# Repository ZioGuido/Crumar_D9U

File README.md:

# GMLAB_D9U
This is the Arduino project for GMLAB D9U, an open source DIY drawbar controller.
Please refer to the included PDF for details about the project, the code and the electronics.

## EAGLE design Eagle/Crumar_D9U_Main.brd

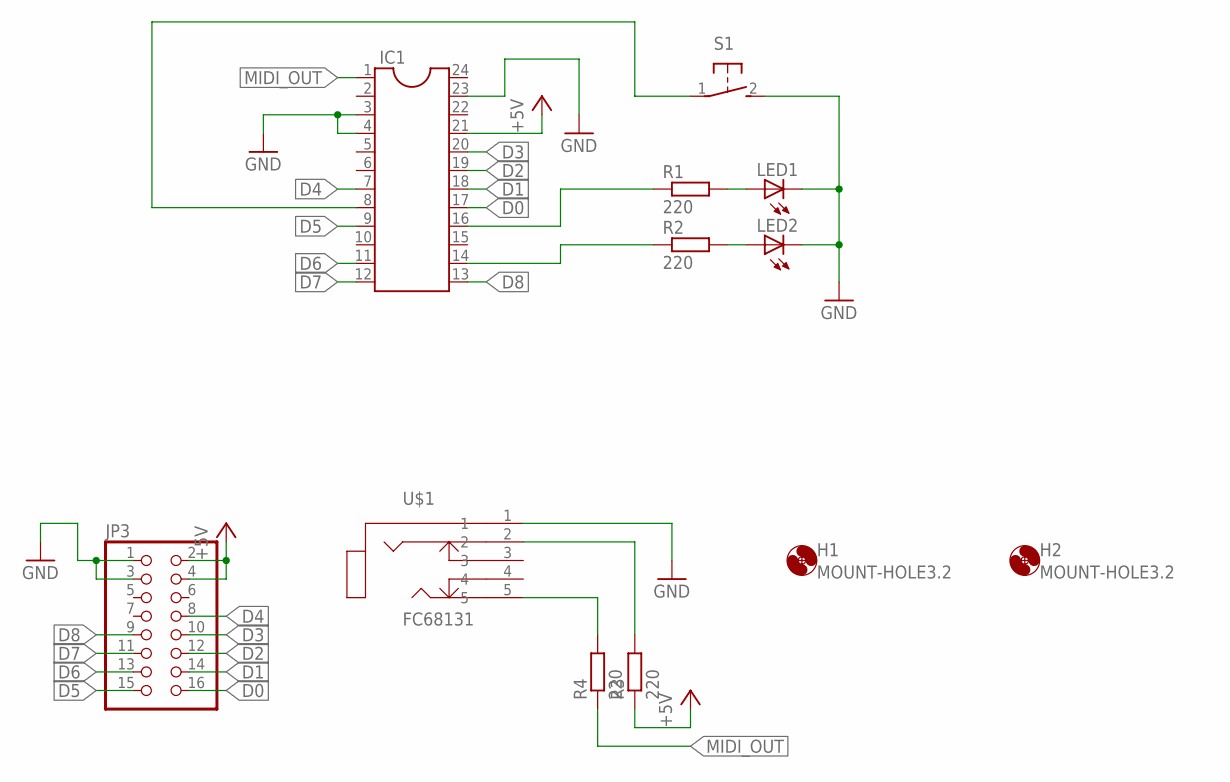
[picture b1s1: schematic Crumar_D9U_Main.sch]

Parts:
H1, H2: MOUNT-HOLE3.2; 3,2
IC1: DIL24-6
JP3: PINHD-2X8; 2X08
LED1, LED2: LED3MM
R1, R2, R3, R4: 220; 0207/7
S1: 31-XX; B3F-31XX
U$1: FC68131; FC68131-5P

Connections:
+5V: IC1.21, JP3.2, JP3.4, R3.1
D0: IC1.17, JP3.16
D1: IC1.18, JP3.14
D2: IC1.19, JP3.12
D3: IC1.20, JP3.10
D4: IC1.7, JP3.8
D5: IC1.9, JP3.15
D6: IC1.11, JP3.13
D7: IC1.12, JP3.11
D8: IC1.13, JP3.9
GND: IC1.3, IC1.4, IC1.23, JP3.1, JP3.3, LED1.K (C), LED2.K (C), S1.2 (S), U$1.1
LED1: IC1.16, R1.1
LED2: IC1.14, R2.1
MIDI_OUT: IC1.1, R4.1
unnamed: LED2.A, R2.2
unnamed: LED1.A, R1.2
unnamed: R3.2, U$1.2
unnamed: R4.2, U$1.5
SW: IC1.8, S1.1

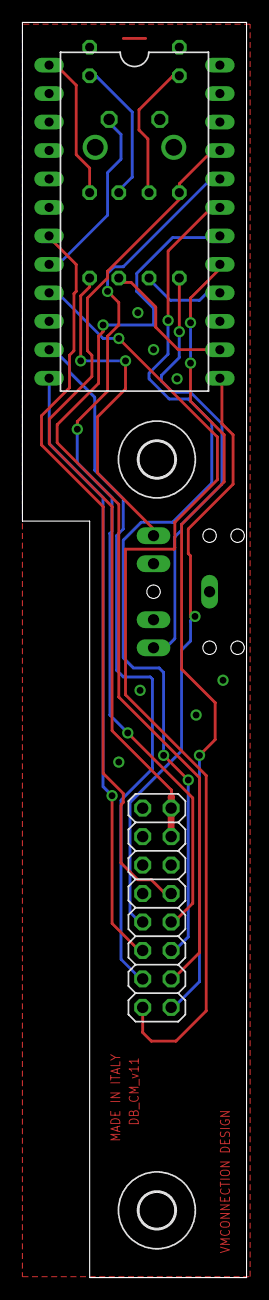
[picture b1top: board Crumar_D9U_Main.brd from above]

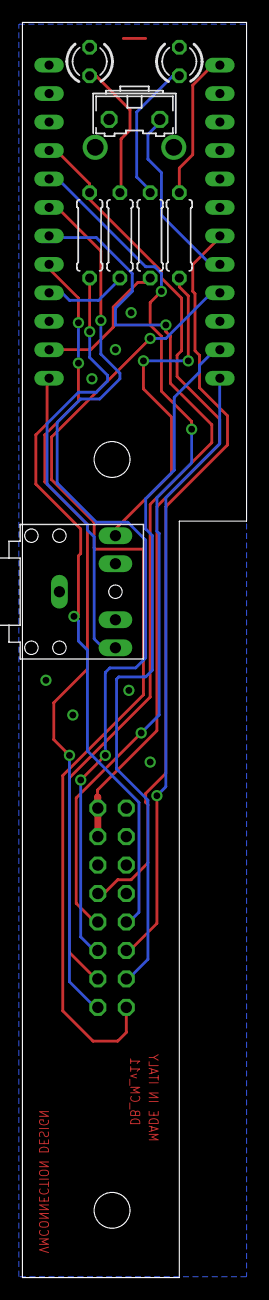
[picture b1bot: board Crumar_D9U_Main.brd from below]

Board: 2 copper layers, 20.0 x 112.0 mm, 12 parts (8 on the bottom side), 19 nets.

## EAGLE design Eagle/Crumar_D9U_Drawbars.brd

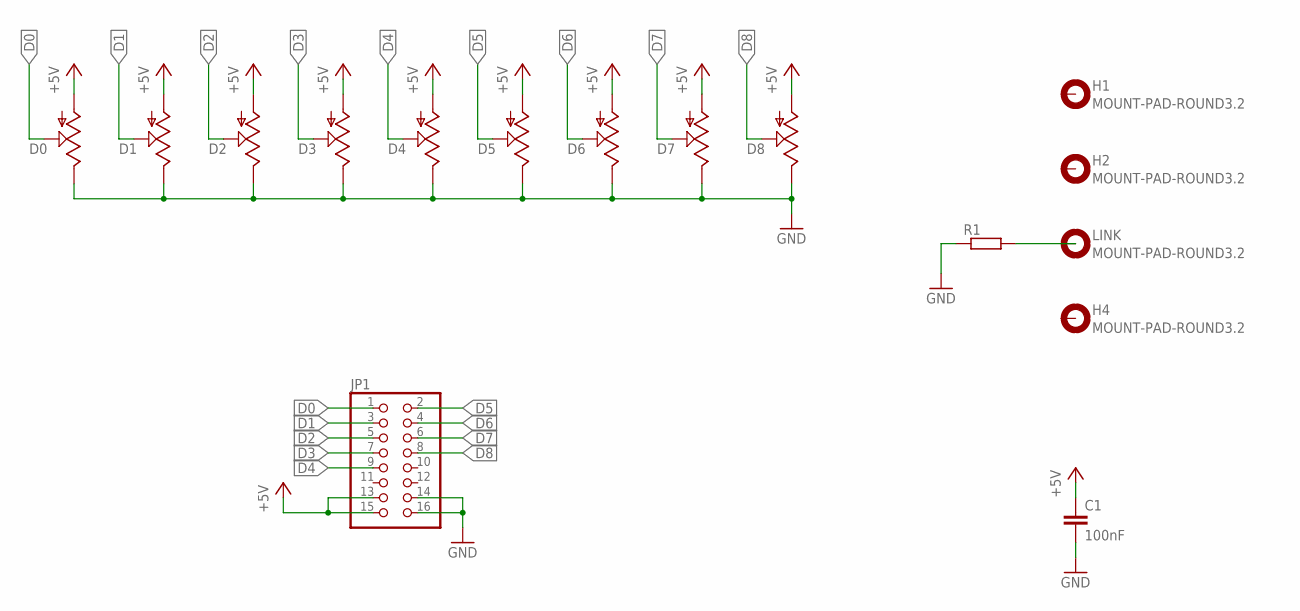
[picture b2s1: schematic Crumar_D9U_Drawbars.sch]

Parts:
C1: 100nF; C050-024X044
D0, D1, D2, D3, D4, D5, D6, D7, D8: POTENTIOMETER; ALPHA_DRAWBARS
H1, H2, H4: MOUNT-PAD-ROUND3.2; 3,2-PAD
JP1: PINHD-2X8; 2X08
LINK: MOUNT-PAD-ROUND3.2; 3,2-PAD
R1: R-EU_0207/12; 0207/12

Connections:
+5V: C1.1, D0.P$2 (1), D1.P$2 (1), D2.P$2 (1), D3.P$2 (1), D4.P$2 (1), D5.P$2 (1), D6.P$2 (1), D7.P$2 (1), D8.P$2 (1), JP1.13, JP1.15
D0: D0.P$3 (2), JP1.1
D1: D1.P$3 (2), JP1.3
D2: D2.P$3 (2), JP1.5
D3: D3.P$3 (2), JP1.7
D4: D4.P$3 (2), JP1.9
D5: D5.P$3 (2), JP1.2
D6: D6.P$3 (2), JP1.4
D7: D7.P$3 (2), JP1.6
D8: D8.P$3 (2), JP1.8
GND: C1.2, D0.P$1 (3), D1.P$1 (3), D2.P$1 (3), D3.P$1 (3), D4.P$1 (3), D5.P$1 (3), D6.P$1 (3), D7.P$1 (3), D8.P$1 (3), JP1.14, JP1.16, R1.1
LINK: R1.2

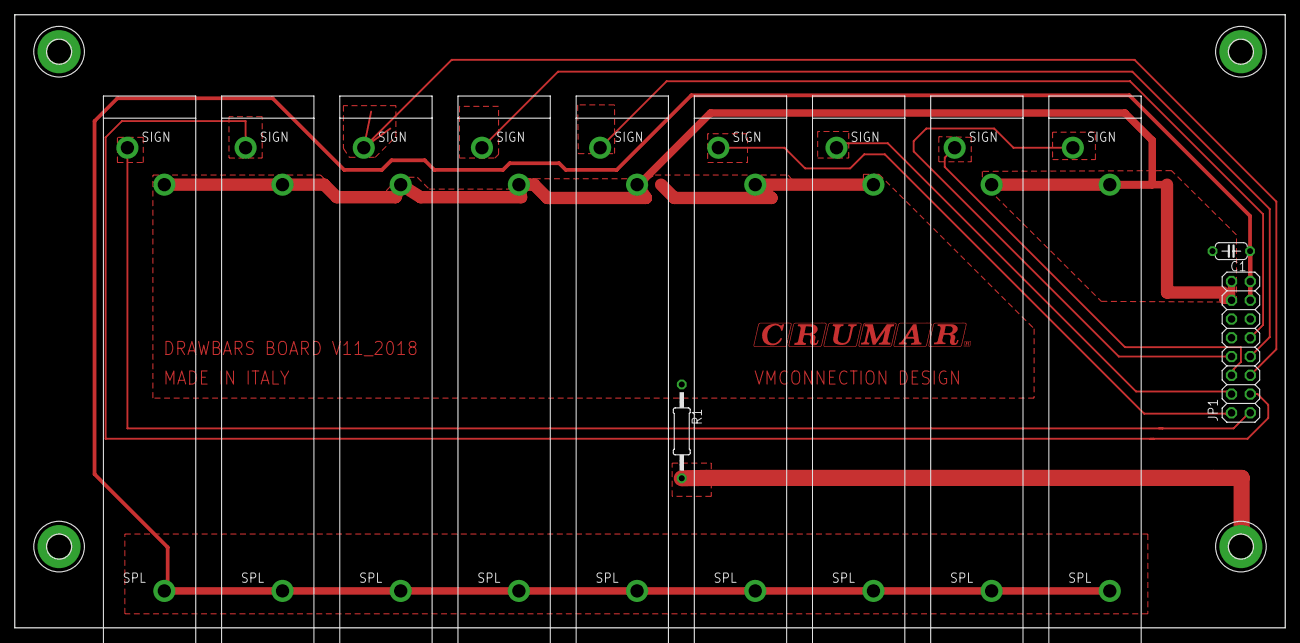
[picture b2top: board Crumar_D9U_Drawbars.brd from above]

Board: 2 copper layers, 172.0 x 83.0 mm, 17 parts (0 on the bottom side), 11 nets.

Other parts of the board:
U$1: CRUMAR3CMTOP

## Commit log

2023-02-22 Now always sends on Midi ch. 1
